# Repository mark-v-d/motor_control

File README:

Servo motor controller. Consisting of two boards, one power and one
control board. The design is made in kicad.

Working supply voltage from 50V to 650V, output current depends on used
MOSFETs but using the Rohm SCT4018 (and sufficient cooling) 20A should
not be a problem.

Currently supported encoders:

Hiperface (make sure to set the powersupply voltage to 8V instead of 12V)
Mitubishi HC-MFS and HC-PQ
CUI AMT213A-V

Additionally linear scales using incremental encoders and index pulses
can be used.

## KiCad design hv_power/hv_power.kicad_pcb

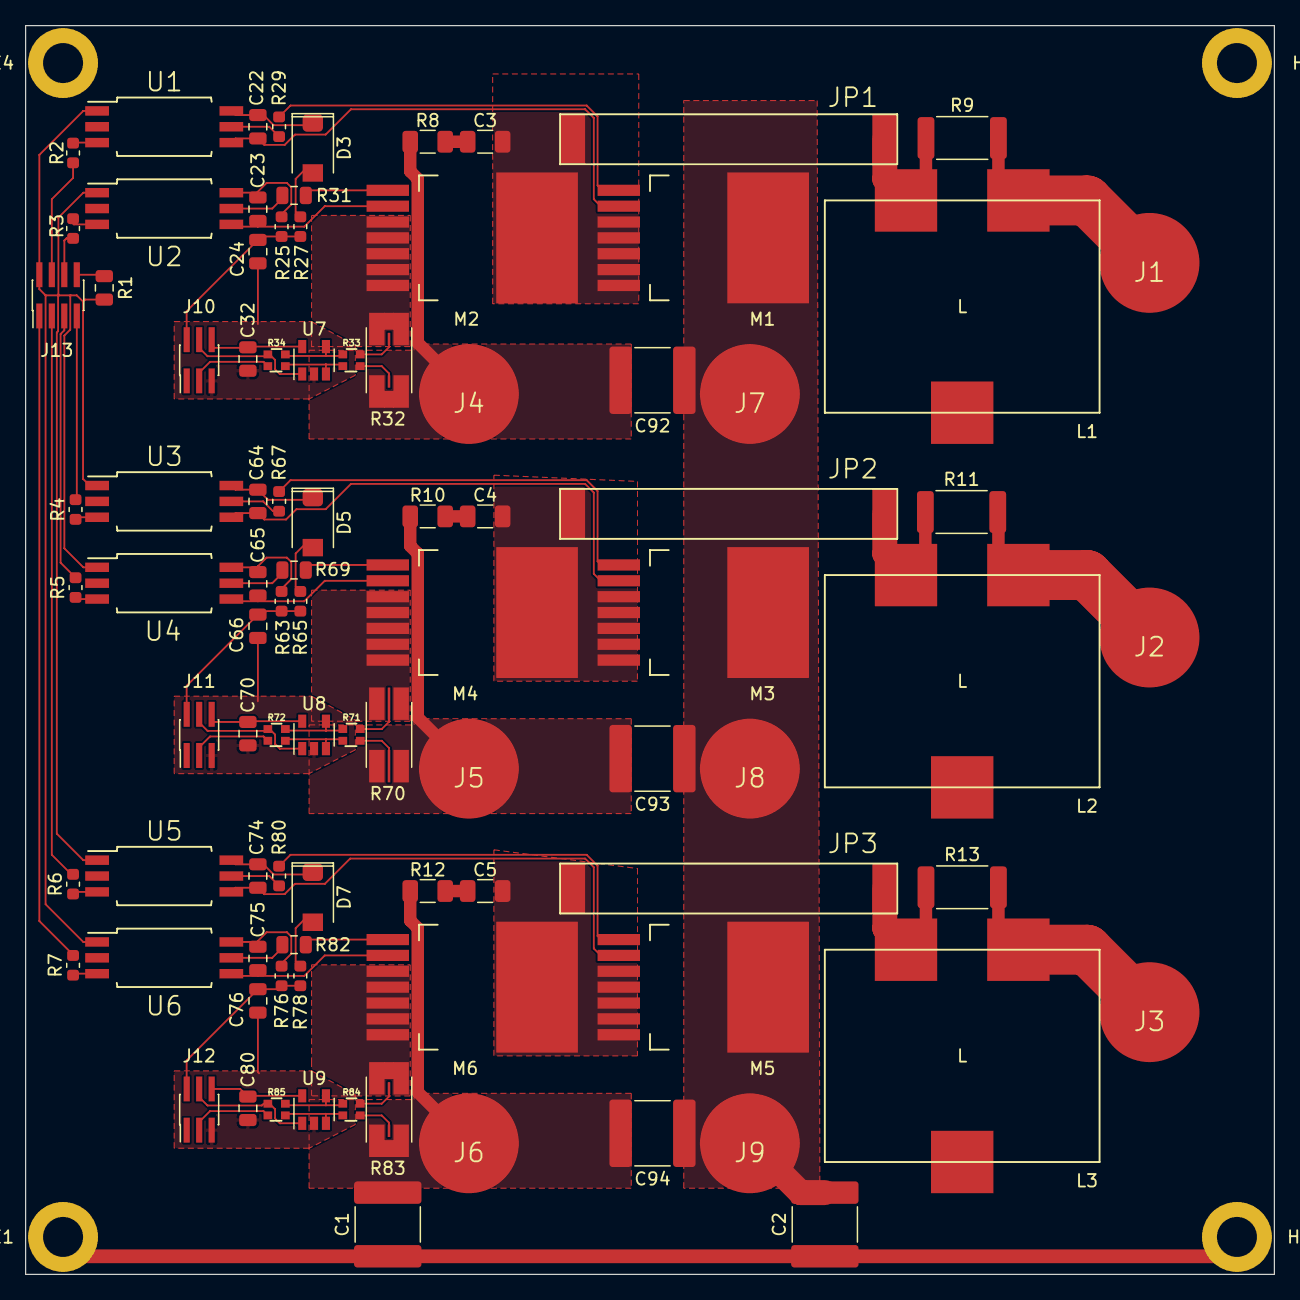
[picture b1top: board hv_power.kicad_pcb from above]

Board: 2 copper layers, 100.0 x 100.0 mm, 95 parts (0 on the bottom side), 88 nets.

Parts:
C1, C2: 3.3nF; C_2220_5650Metric
C3, C4, C5: C; C_1206_3216Metric
C22, C23, C24, C64, C65, C66, C74, C75, C76: 1uF; C_0805_2012Metric
C32, C70, C80: 100nF; C_0805_2012Metric
C92, C93, C94: 100nF; C_2220_5650Metric
D3, D5, D7: STTH112A; D_SMA
HOLE1, HOLE4: HOLE; MountingHole_3.2mm_M3_DIN965_Pad
HOLE2, HOLE3: HOLE; MountingHole_3.2mm_M3_DIN965_Pad_ScreenAlignment
J1, J2, J3: Conn_01x01_Male; Wurth_7466204
J4, J5, J6: V-; Wurth_7466204
J7, J8, J9: V+; Wurth_7466204
J10, J11, J12: Conn_02x03_Odd_Even; PinHeader_2x03_P1.00mm_Vertical_SMD
J13: Conn_02x04_Odd_Even; PinHeader_2x04_P1.00mm_Vertical_SMD
JP1, JP2, JP3: Jumper_2_Bridged; jumper_3x25mm
L1, L2, L3: L; WE-HCF2013
M1, M2, M3, M4, M5, M6: TBD; TO-263-7-GDSKS_novias
R1: NTC; R_0805_2012Metric
R2, R3, R4, R5, R6, R7: 270; R_0603_1608Metric
R8, R10, R12: R; R_1206_3216Metric
R9, R11, R13: 270; R_2512_6332Metric
R25, R27, R29, R63, R65, R67, R76, R78, R80: 4.7; R_0603_1608Metric
R31, R69, R82: 4.7; R_0805_2012Metric
R32, R70, R83: R_Shunt; R_2512_Shunt_Rohm_PMR100_3.0m
R33, R71, R84: 100; ACASN
R34, R72, R85: 2k; ACASN
U1, U2, U3, U4, U5, U6: UCC23511DWY; SOIC-6_7.5x4.68mm_P1.27mm
U7, U8, U9: TSV991ILT; SOT-23-5

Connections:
+3.3V: J13.2, R1.1, U1.1 (anode), U2.1 (anode), U3.1 (anode), U4.1 (anode), U5.1 (anode), U6.1 (anode)
+800V: C2.2, C92.1, C93.1, C94.1, J7.1, J8.1, J9.1, M1.D, M3.D, M5.D
/HBH0: J13.4, R2.2
/HBH1: J13.7, R4.2
/HBH2: J13.3, R6.2
/HBL0: J13.6, R3.2
/HBL1: J13.5, R5.2
/HBL2: J13.1, R7.2
/H_Bridge0/0: C24.1, C32.2, J10.5, U7.2 (V-)
/H_Bridge0/+3.3: C32.1, J10.6, U7.5 (V+)
/H_Bridge0/+12: C24.2, J10.2, R25.2, R27.1
/H_Bridge0/CS: M2.S, R32.1
/H_Bridge0/C_N: J10.4, R34.1, U7.1
/H_Bridge0/C_P: J10.3, R34.2
/H_Bridge0/I_N: R33.1, R34.4, U7.4 (-)
/H_Bridge0/I_P: R33.2, R34.3, U7.3 (+)
/H_Bridge0/V-: C92.2, J4.1, R8.2, R32.4
/H_Bridge0/d1: R2.1, U1.3 (cathode)
/H_Bridge0/d2: R3.1, U2.3 (cathode)
/H_Bridge0/sw: C3.1, JP1.1 (A), M1.S, M2.D
/H_Bridge0/sw_+: C22.1, D3.C, U1.6 (vcc)
/H_Bridge0/sw_g: M1.G, R29.1
/H_Bridge0/sw_m1: JP1.2 (B), L1.2, R9.1
/H_Bridge0/sw_m2: J1.1, L1.1, R9.2
/H_Bridge0/sw_o: R29.2, U1.5 (out)
/H_Bridge0/sw_s: C22.2, M1.KS (ks), U1.4 (gnd)
/H_Bridge0/x: C3.2, R8.1
/H_Bridge1/0: C66.1, C70.2, J11.5, U8.2 (V-)
/H_Bridge1/+3.3: C70.1, J11.6, U8.5 (V+)
/H_Bridge1/+12: C66.2, J11.2, R63.2, R65.1
/H_Bridge1/CS: M4.S, R70.1
/H_Bridge1/C_N: J11.4, R72.1, U8.1
/H_Bridge1/C_P: J11.3, R72.2
/H_Bridge1/I_N: R71.1, R72.4, U8.4 (-)
/H_Bridge1/I_P: R71.2, R72.3, U8.3 (+)
/H_Bridge1/V-: C93.2, J5.1, R10.2, R70.4
/H_Bridge1/d1: R4.1, U3.3 (cathode)
/H_Bridge1/d2: R5.1, U4.3 (cathode)
/H_Bridge1/sw: C4.1, JP2.1 (A), M3.S, M4.D
/H_Bridge1/sw_+: C64.1, D5.C, U3.6 (vcc)
/H_Bridge1/sw_g: M3.G, R67.1
/H_Bridge1/sw_m1: JP2.2 (B), L2.2, R11.1
/H_Bridge1/sw_m2: J2.1, L2.1, R11.2
/H_Bridge1/sw_o: R67.2, U3.5 (out)
/H_Bridge1/sw_s: C64.2, M3.KS (ks), U3.4 (gnd)
/H_Bridge1/x: C4.2, R10.1
/H_Bridge2/0: C76.1, C80.2, J12.5, U9.2 (V-)
/H_Bridge2/+3.3: C80.1, J12.6, U9.5 (V+)
/H_Bridge2/+12: C76.2, J12.2, R76.2, R78.1
/H_Bridge2/CS: M6.S, R83.1
/H_Bridge2/C_N: J12.4, R85.1, U9.1
/H_Bridge2/C_P: J12.3, R85.2
/H_Bridge2/I_N: R84.1, R85.4, U9.4 (-)
/H_Bridge2/I_P: R84.2, R85.3, U9.3 (+)
/H_Bridge2/V-: C1.2, C94.2, J6.1, R12.2, R83.4
/H_Bridge2/d1: R6.1, U5.3 (cathode)
/H_Bridge2/d2: R7.1, U6.3 (cathode)
/H_Bridge2/sw: C5.1, JP3.1 (A), M5.S, M6.D
/H_Bridge2/sw_+: C74.1, D7.C, U5.6 (vcc)
/H_Bridge2/sw_g: M5.G, R80.1
/H_Bridge2/sw_m1: JP3.2 (B), L3.2, R13.1
/H_Bridge2/sw_m2: J3.1, L3.1, R13.2
/H_Bridge2/sw_o: R80.2, U5.5 (out)
/H_Bridge2/sw_s: C74.2, M5.KS (ks), U5.4 (gnd)
/H_Bridge2/x: C5.2, R12.1
/ntc: J13.8, R1.2
/pe: C1.1, C2.1, HOLE1.1, HOLE2.1
unnamed: D3.A, R27.2
unnamed: D5.A, R65.2
unnamed: D7.A, R78.2
unnamed: M2.G, R31.1
unnamed: C23.2, M2.KS (ks), U2.4 (gnd)
unnamed: M4.G, R69.1
unnamed: C65.2, M4.KS (ks), U4.4 (gnd)
unnamed: M6.G, R82.1
unnamed: C75.2, M6.KS (ks), U6.4 (gnd)
unnamed: R32.2, R33.4
unnamed: R32.3, R33.3
unnamed: R70.2, R71.4
unnamed: R70.3, R71.3
unnamed: R83.2, R84.4
unnamed: R83.3, R84.3
unnamed: R31.2, U2.5 (out)
unnamed: C23.1, R25.1, U2.6 (vcc)
unnamed: R69.2, U4.5 (out)
unnamed: C65.1, R63.1, U4.6 (vcc)
unnamed: R82.2, U6.5 (out)
unnamed: C75.1, R76.1, U6.6 (vcc)

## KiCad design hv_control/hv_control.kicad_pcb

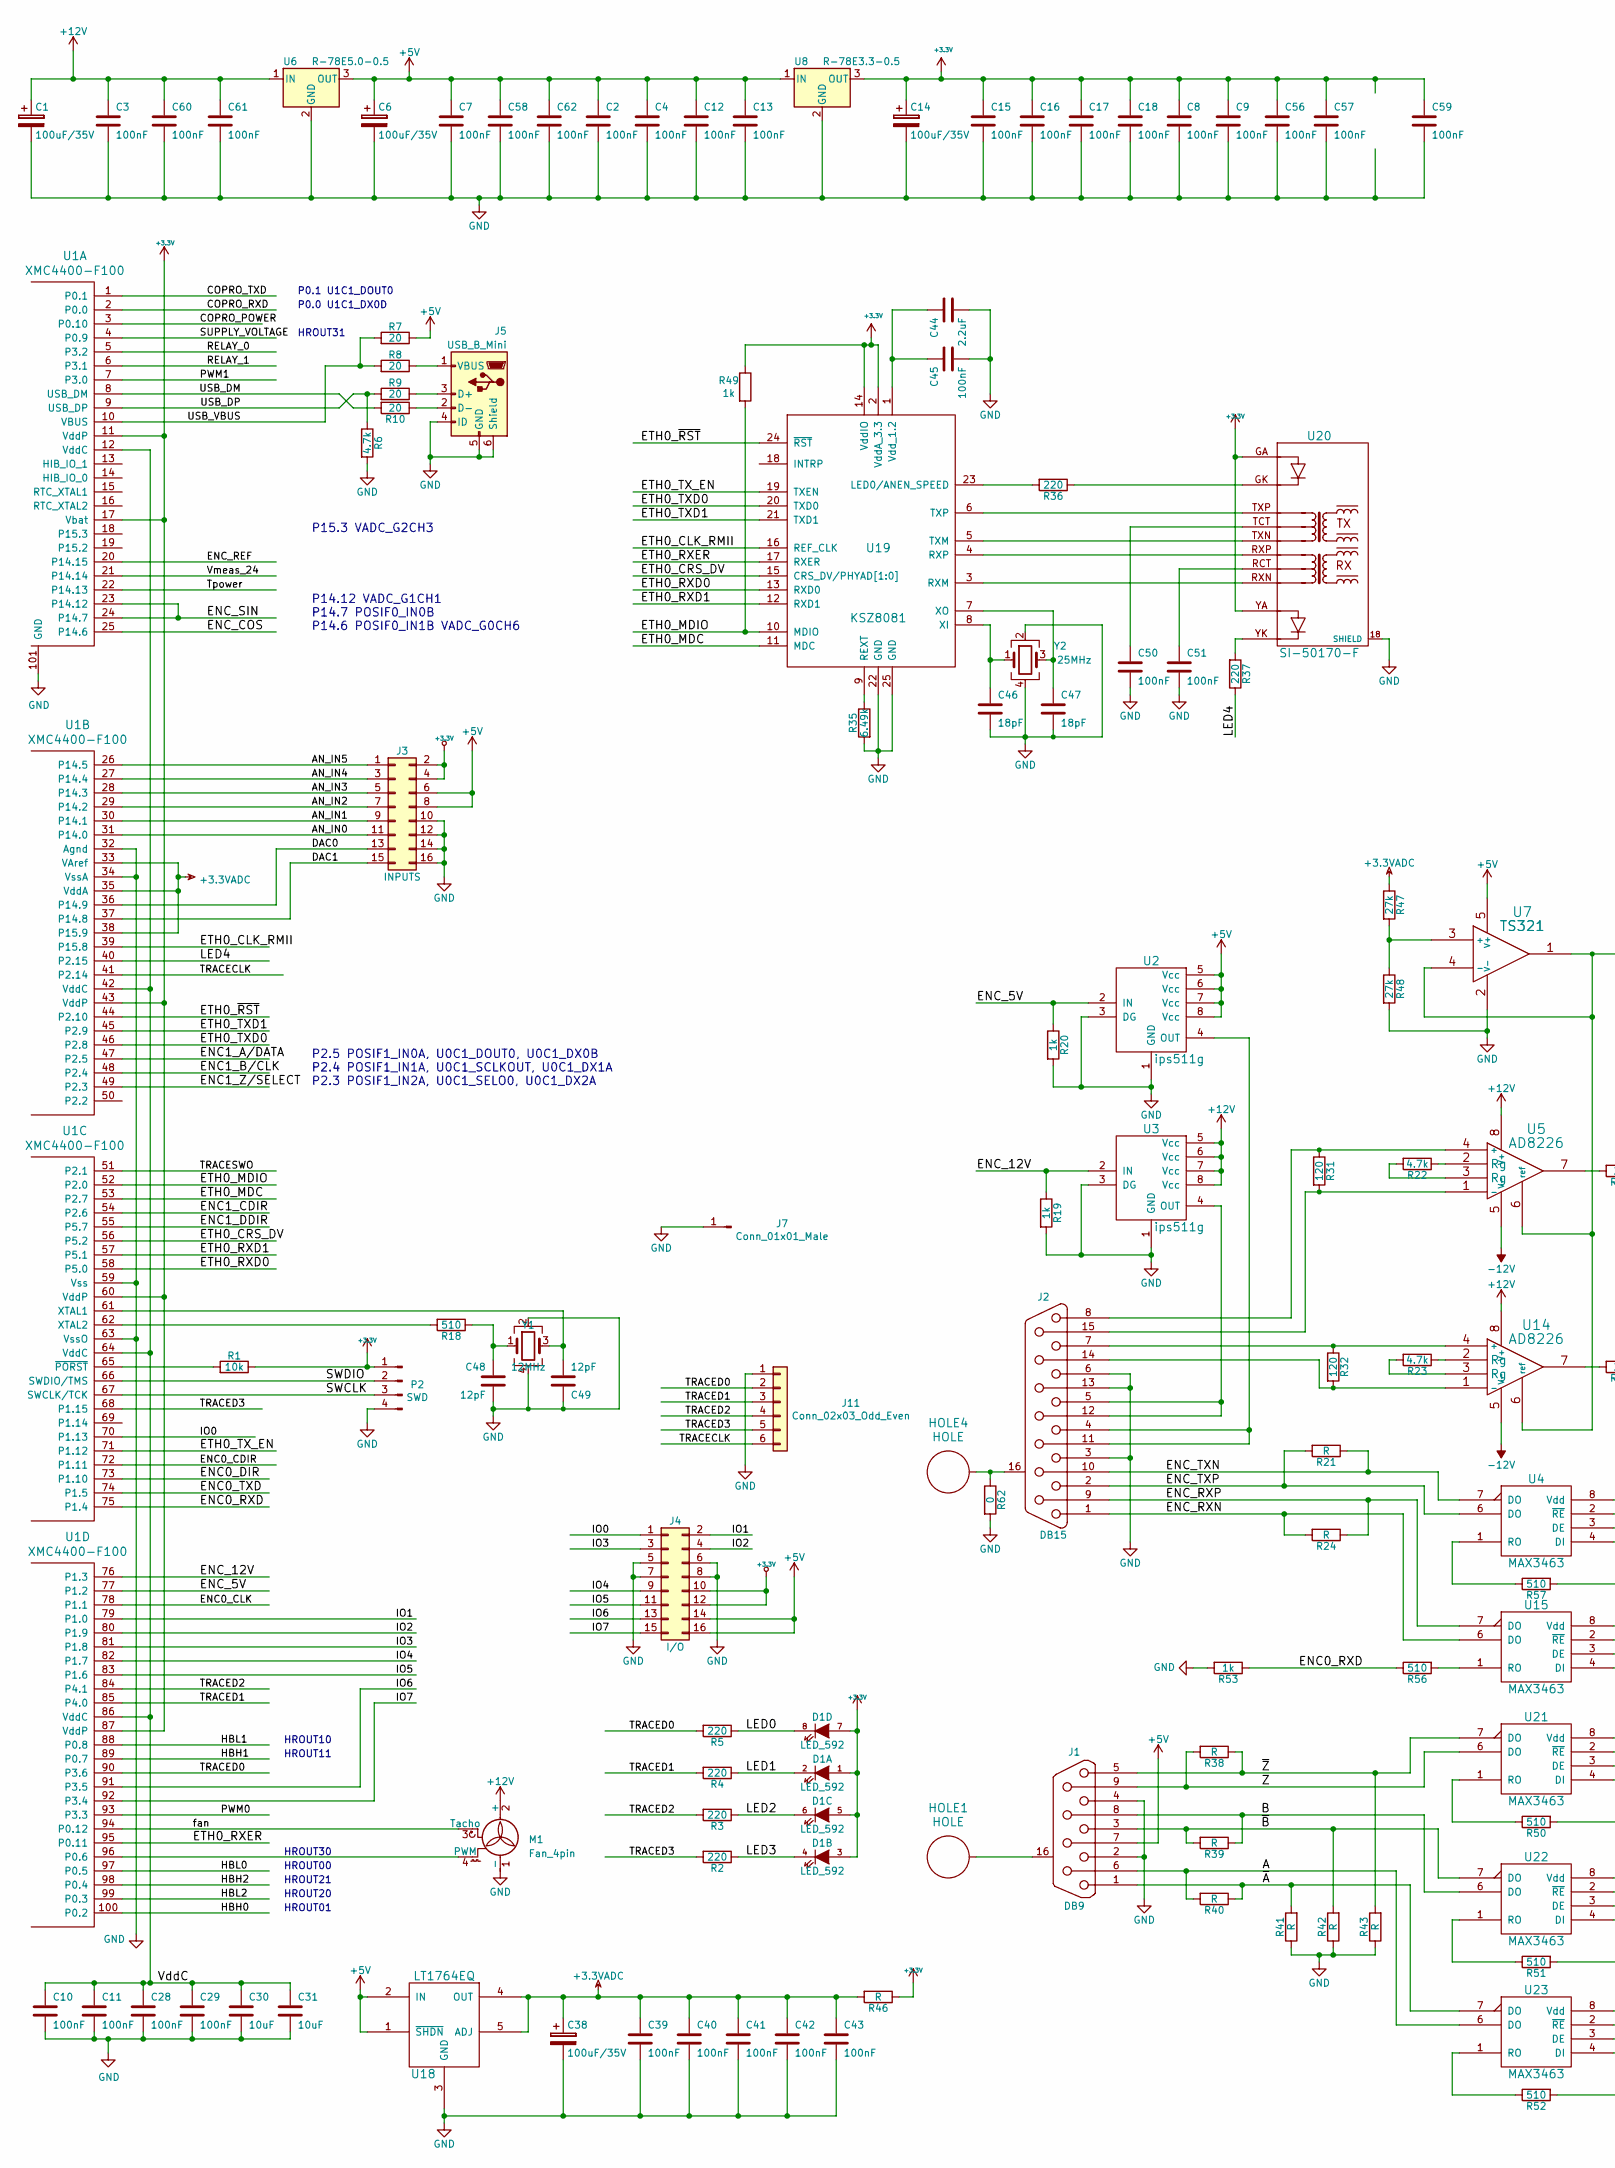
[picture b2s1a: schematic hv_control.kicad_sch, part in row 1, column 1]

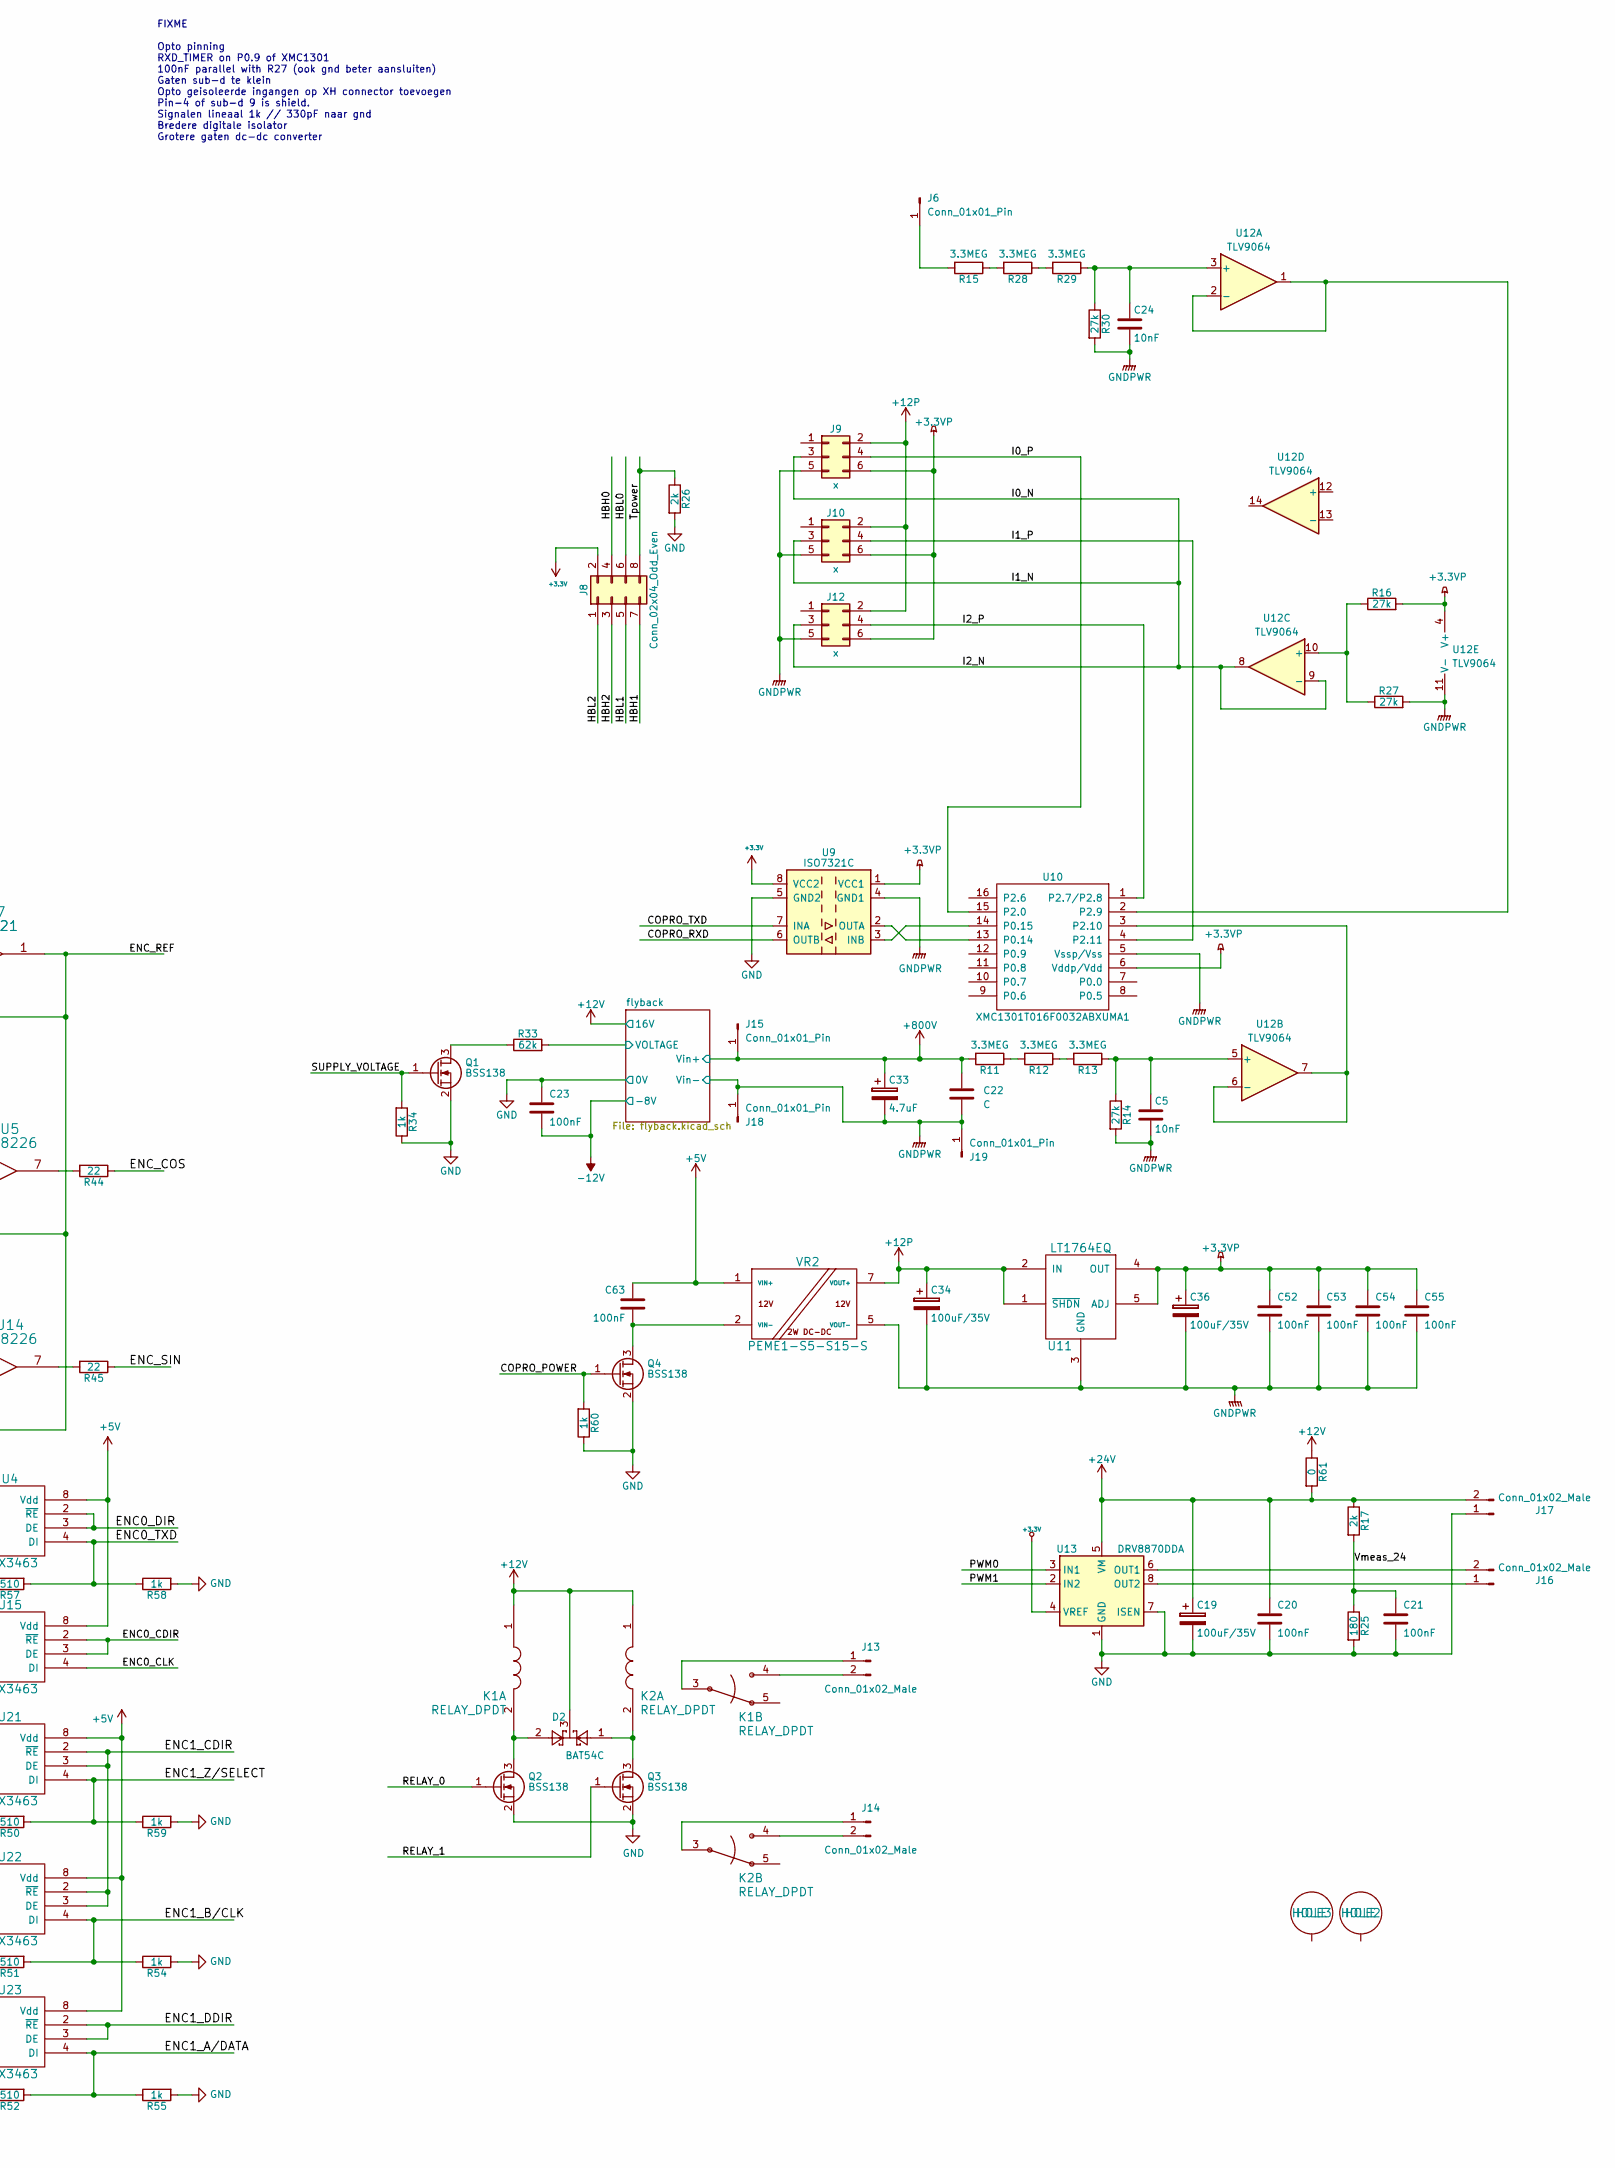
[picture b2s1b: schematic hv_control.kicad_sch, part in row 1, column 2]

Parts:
C1, C6, C14, C19, C34, C36, C38: 100uF/35V; CP_Elec_8x10.5; PartNr EEEFK1V101P
C2, C3, C4, C7, C8, C9, C10, C11, C12, C13, C15, C16, C17, C18, C20, C21, C23, C28, C29, C39, C40, C41, C42, C43, C45, C50, C51, C52, C54, C55, C56, C57, C58, C59, C60, C61, C62, C63: 100nF; C_0603_1608Metric
C5, C24: 10nF; C_0603_1608Metric
C22: C; C_Rect_L18.0mm_W6.0mm_P15.00mm_FKS3_FKP3
C30, C31: 10uF; C_1210_3225Metric
C33: 4.7uF; CP_Elec_10x14.3; PartNr EEVEB2G4R7Q
C44: 2.2uF; C_1206_3216Metric
C46, C47: 18pF; C_0603_1608Metric
C48, C49: 12pF; C_0603_1608Metric
C53: 100nF; C_0805_2012Metric
D1: LED_592; LED_592-3030-013F
D2: BAT54C; SOT-23
HOLE1, HOLE2: HOLE; MountingHole_3.2mm_M3_DIN965_Pad_ScreenAlignment
HOLE3, HOLE4: HOLE; MountingHole_3.2mm_M3_DIN965_Pad
J1: DB9; DB9F_ebay; PartNr 1734354-1; Farnell 1653978
J2: DB15; DB15F_ebay; PartNr 1-106506-2; Farnell 3417207
J3: INPUTS; PinHeader_2x08_P2.54mm_Vertical
J4: I/O; PinHeader_2x08_P2.54mm_Vertical
J5: USB_B_Mini; USB_Micro-B_Molex-105017-0001
J6, J15, J18, J19: Conn_01x01_Pin; Pin_D1.4mm_L8.5mm_W2.8mm_FlatFork
J7: Conn_01x01_Male; PinHeader_1x01_P2.54mm_Vertical
J8: Conn_02x04_Odd_Even; PinSocket_2x04_P1.00mm_Vertical_SMD; PartNr CLM-104-02-F-D; Digikey SAM15174-ND
J9, J10, J12: x; PinSocket_2x03_P1.00mm_Vertical_SMD; PartNr CLM-103-02-F-D; Digikey SAM12591-ND
J11: Conn_02x03_Odd_Even; PinHeader_1x06_P2.54mm_Vertical
J13, J14, J16, J17: Conn_01x02_Male; pin_2_5mm
K1, K2: RELAY_DPDT; T77
M1: Fan_4pin; FanPinHeader_1x04_P2.54mm_Vertical; PartNr 47053-3000; Mouser 538-47053-3000
P2: SWD; PinHeader_1x04_P2.54mm_Vertical
Q1, Q2, Q3, Q4: BSS138; SOT-23
R1: 10k; R_0603_1608Metric
R2, R3, R4, R5, R36, R37: 220; R_0603_1608Metric
R6, R22, R23: 4.7k; R_0603_1608Metric
R7: 20; R_0805_2012Metric
R8, R9, R10: 20; R_0603_1608Metric
R11, R12, R13, R15, R28, R29: 3.3MEG; R_1206_3216Metric
R14, R16, R27, R30, R47, R48: 27k; R_0603_1608Metric
R17, R26: 2k; R_0603_1608Metric
R18, R50, R51, R52, R56, R57: 510; R_0603_1608Metric
R19, R20, R34, R49, R53, R54, R55, R58, R59, R60: 1k; R_0603_1608Metric
R21, R24, R38, R39, R40, R41, R42, R43, R46: R; R_0603_1608Metric
R25: 180; R_0603_1608Metric
R31, R32: 120; R_0603_1608Metric
R33: 62k; R_0603_1608Metric
R35: 6.49k; R_0603_1608Metric
R44, R45: 22; R_0603_1608Metric
R61: 0; R_0805_2012Metric
R62: 0; R_0603_1608Metric
U1: XMC4400-F100; TQFP-100-1EP_14x14mm_P0.5mm_EP5x5mm; Farnell 2418735
U2, U3: ips511g; SOIC-8_3.9x4.9mm_P1.27mm
U4, U15, U21, U22, U23: MAX3463; SOIC-8_3.9x4.9mm_P1.27mm
U5, U14: AD8226; SOIC-8_3.9x4.9mm_P1.27mm; Farnell 1827360
U6: R-78E5.0-0.5; Converter_DCDC_RECOM_R-78E-0.5_THT
U7: TS321; SOT-23-5; PartNr TS321AILT; Farnell 1750165
U8: R-78E3.3-0.5; Converter_DCDC_RECOM_R-78E-0.5_THT
U9: ISO7321C; SOIC-8_3.9x4.9mm_P1.27mm; Digikey 296-42102-1-ND
U10: XMC1301T016F0032ABXUMA1; TSSOP-16_4.4x5mm_P0.65mm; Digikey XMC1301T016F0032ABXUMA1CT-ND
U11, U18: LT1764EQ; DD-PAK
U12: TLV9064; SOIC-14_3.9x8.7mm_P1.27mm
U13: DRV8870DDA; Texas_HTSOP-8-1EP_3.9x4.9mm_P1.27mm_EP2.95x4.9mm_Mask2.4x3.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; Digikey 296-42660-1-ND
U19: KSZ8081; QFN-24-1EP_4x4mm_P0.5mm_EP2.6x2.6mm; PartNr KSZ8081RNACA-TR; Farnell 2509802
U20: SI-50170-F; ETH100_MAG; PartNr SI-50170-F; Farnell 2676003
VR2: PEME1-S5-S15-S; RKZXXXXS; Digikey 102-6340-ND
Y1: 12MHz; Crystal_SMD_SeikoEpson_FA238-4Pin_3.2x2.5mm; PartNr QC3CA12.0000F12B23M; Farnell 2508630
Y2: 25MHz; Crystal_SMD_SeikoEpson_FA238-4Pin_3.2x2.5mm; PartNr QC3CA25.0000F18B23M; Farnell 2508942

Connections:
+3.3V: C8.1, C9.1, C14.1, C15.1, C16.1, C17.1, C18.1, C56.1, C57.1, C59.1, D1.1 (A), D1.3 (A), D1.5 (A), D1.7 (A), J3.2, J3.4, J4.10, J4.12, J8.2, P2.1, R1.1, R46.1, R49.1, U1.11 (VddP), U1.17 (Vbat), U1.43 (VddP), U1.60 (VddP), U1.87 (VddP), U8.3 (OUT), U9.8 (VCC2), U13.4 (VREF), U19.2 (VddA_3.3), U19.14 (VddIO), U20.GA, U20.YA
+3.3VADC: C38.1, C39.1, C40.1, C41.1, C42.1, C43.1, R46.2, R47.1, U1.33 (VAref), U1.35 (VddA), U1.38 (P15.9), U18.4 (OUT), U18.5 (ADJ)
+3.3VP: C36.1, C52.1, C53.1, C54.1, C55.1, J9.6, J10.6, J12.6, R16.2, U9.1 (VCC1), U10.6 (Vddp/Vdd), U11.4 (OUT), U11.5 (ADJ), U12.4 (V+)
+5V: C2.1, C4.1, C6.1, C7.1, C12.1, C13.1, C58.1, C62.1, C63.1, J1.7, J3.6, J3.8, J4.14, J4.16, R7.1, U2.5 (Vcc), U2.6 (Vcc), U2.7 (Vcc), U2.8 (Vcc), U4.8 (Vdd), U6.3 (OUT), U7.5 (V+), U8.1 (IN), U15.8 (Vdd), U18.1 (~SHDN), U18.2 (IN), U21.8 (Vdd), U22.8 (Vdd), U23.8 (Vdd), VR2.1 (VIN+)
+12P: C34.1, J9.2, J10.2, J12.2, U11.1 (~SHDN), U11.2 (IN), VR2.7 (VOUT+)
+24V: C19.1, C20.1, J17.2, R17.1, R61.2, U13.5 (VM)
+800V: C22.1, J15.1, R11.2; also elsewhere on the board
-12V: C23.2, U5.5 (V-), U14.5 (V-); also elsewhere on the board
/A: J1.6, R40.2, U23.6 (DO)
/AN_IN0: J3.11, U1.31 (P14.0)
/AN_IN1: J3.9, U1.30 (P14.1)
/AN_IN2: J3.7, U1.29 (P14.2)
/AN_IN3: J3.5, U1.28 (P14.3)
/AN_IN4: J3.3, U1.27 (P14.4)
/AN_IN5: J3.1, U1.26 (P14.5)
/B: J1.8, R39.1, U22.6 (DO)
/COPRO_POWER: Q4.1 (G), R60.2, U1.3 (P0.10)
/COPRO_RXD: U1.2 (P0.0), U9.6 (OUTB)
/COPRO_TXD: U1.1 (P0.1), U9.7 (INA)
/DAC0: J3.13, U1.36 (P14.9)
/DAC1: J3.15, U1.37 (P14.8)
/ENC0_CDIR: U1.72 (P1.11), U15.2 (~RE), U15.3 (DE)
/ENC0_CLK: U1.78 (P1.1), U15.4 (DI)
/ENC0_DIR: U1.73 (P1.10), U4.2 (~RE), U4.3 (DE)
/ENC0_RXD: R53.1, R56.1, U1.75 (P1.4)
/ENC0_TXD: R57.2, R58.1, U1.74 (P1.5), U4.4 (DI)
/ENC1_A/DATA: R52.2, R55.1, U1.47 (P2.5), U23.4 (DI)
/ENC1_B/CLK: R51.2, R54.1, U1.48 (P2.4), U22.4 (DI)
/ENC1_CDIR: U1.54 (P2.6), U21.2 (~RE), U21.3 (DE), U22.2 (~RE), U22.3 (DE)
/ENC1_DDIR: U1.55 (P5.7), U23.2 (~RE), U23.3 (DE)
/ENC1_Z/SELECT: R50.2, R59.1, U1.49 (P2.3), U21.4 (DI)
/ENC_5V: R20.1, U1.77 (P1.2), U2.2 (IN)
/ENC_12V: R19.1, U1.76 (P1.3), U3.2 (IN)
/ENC_COS: R44.1, U1.25 (P14.6)
/ENC_REF: U1.20 (P14.15), U5.6 (ref), U7.1, U7.4 (-), U14.6 (ref)
/ENC_RXN: J2.1, R24.2, U15.6 (DO)
/ENC_RXP: J2.9, R24.1, U15.7 (DO)
/ENC_SIN: R45.1, U1.23 (P14.12), U1.24 (P14.7)
/ENC_TXN: J2.10, R21.1, U4.7 (DO)
/ENC_TXP: J2.2, R21.2, U4.6 (DO)
/ETH0_CLK_RMII: U1.39 (P15.8), U19.16 (REF_CLK)
/ETH0_CRS_DV: U1.56 (P5.2), U19.15 (CRS_DV/PHYAD[1:0])
/ETH0_MDC: U1.53 (P2.7), U19.11 (MDC)
/ETH0_MDIO: R49.2, U1.52 (P2.0), U19.10 (MDIO)
/ETH0_RXD0: U1.58 (P5.0), U19.13 (RXD0)
/ETH0_RXD1: U1.57 (P5.1), U19.12 (RXD1)
/ETH0_RXER: U1.95 (P0.11), U19.17 (RXER)
/ETH0_TXD0: U1.46 (P2.8), U19.20 (TXD0)
/ETH0_TXD1: U1.45 (P2.9), U19.21 (TXD1)
/ETH0_TX_EN: U1.71 (P1.12), U19.19 (TXEN)
/ETH0_~RST: U1.44 (P2.10), U19.24 (~RST)
/HBH0: J8.4, U1.100 (P0.2)
/HBH1: J8.7, U1.89 (P0.7)
/HBH2: J8.3, U1.98 (P0.4)
/HBL0: J8.6, U1.97 (P0.5)
/HBL1: J8.5, U1.88 (P0.8)
/HBL2: J8.1, U1.99 (P0.3)
/I0_N: J9.3, J10.3, J12.3, U12.8, U12.9 (-)
/I0_P: J9.4, U10.15 (P2.0)
/I1_P: J10.4, U10.4 (P2.11)
/I2_P: J12.4, U10.1 (P2.7/P2.8)
/IO0: J4.1, U1.70 (P1.13)
/IO1: J4.2, U1.79 (P1.0)
/IO2: J4.4, U1.80 (P1.9)
/IO3: J4.3, U1.81 (P1.8)
/IO4: J4.9, U1.82 (P1.7)
/IO5: J4.11, U1.83 (P1.6)
/IO6: J4.13, U1.91 (P3.5)
/IO7: J4.15, U1.92 (P3.4)
/LED0: D1.8 (K), R5.1
/LED1: D1.2 (K), R4.1
/LED2: D1.6 (K), R3.1
/LED3: D1.4 (K), R2.1
/LED4: R37.1, U1.40 (P2.15)
/PWM0: U1.93 (P3.3), U13.3 (IN1)
/PWM1: U1.7 (P3.0), U13.2 (IN2)
/RELAY_0: Q2.1 (G), U1.5 (P3.2)
/RELAY_1: Q3.1 (G), U1.6 (P3.1)
/SWCLK: P2.3, U1.67 (SWCLK/TCK)
/SWDIO: P2.2, U1.66 (SWDIO/TMS)
/TRACECLK: J11.6, U1.41 (P2.14)
/TRACED0: J11.2, R5.2, U1.90 (P3.6)
/TRACED1: J11.3, R4.2, U1.85 (P4.0)
/TRACED2: J11.4, R3.2, U1.84 (P4.1)
/TRACED3: J11.5, R2.2, U1.68 (P1.15)
/TRACESWO: U1.51 (P2.1)
/Tpower: J8.8, R26.1, U1.22 (P14.13)
/USB_DM: R10.2, U1.8 (USB_DM)
/USB_DP: R6.1, R9.2, U1.9 (USB_DP)
/USB_VBUS: R7.2, R8.2, U1.10 (VBUS)
/VddC: C10.1, C11.1, C28.1, C29.1, C30.1, C31.1, U1.12 (VddC), U1.42 (VddC), U1.64 (VddC), U1.86 (VddC)
/Vmeas_24: C21.1, R17.2, R25.1, U1.21 (P14.14)
/Z: J1.9, R38.2, U21.6 (DO)
/fan: M1.3 (Tacho), U1.94 (P0.12)
/flyback/VOLTAGE: R33.2; also elsewhere on the board
/~A: J1.1, R40.1, R41.2, U23.7 (DO)
/~B: J1.3, R39.2, R42.2, U22.7 (DO)
/~Z: J1.5, R38.1, R43.2, U21.7 (DO)
GNDPWR: C5.2, C22.2, C24.2, C34.2, C36.2, C52.2, C53.2, C54.2, C55.2, J9.5, J10.5, J12.5, J18.1, J19.1, R14.2, R27.2, R30.2, U9.4 (GND1), U10.5 (Vssp/Vss), U11.3 (GND), U12.11 (V-), VR2.5 (VOUT-); also elsewhere on the board
unnamed: C48.1, R18.1, Y1.1
unnamed: C50.1, U20.TCT
unnamed: C51.1, U20.RCT
unnamed: HOLE1.1, J1.16
unnamed: HOLE4.1, J2.16, R62.1
unnamed: J2.5, J2.12, U3.4 (OUT)
unnamed: J2.14, R32.2, U14.1 (-)
unnamed: J2.15, R31.2, U5.1 (-)
unnamed: J2.4, J2.11 (P111), U2.4 (OUT)
unnamed: J5.3 (D+), R9.1
unnamed: J5.2 (D-), R10.1
unnamed: J5.1 (VBUS), R8.1
unnamed: J6.1, R15.2
unnamed: J13.1, K1.3 (common)
unnamed: J13.2, K1.4 (break)
unnamed: J14.1, K2.3 (common)
unnamed: J14.2, K2.4 (break)
unnamed: J16.1, U13.8 (OUT2)
unnamed: J16.2, U13.6 (OUT1)
unnamed: D2.2, K1.2 (a2), Q2.3 (D)
unnamed: D2.1, K2.2 (a2), Q3.3 (D)
unnamed: M1.4 (PWM), U1.96 (P0.6)
unnamed: C63.2, Q4.3 (D), VR2.2 (VIN-)
unnamed: R11.1, R12.2
unnamed: R12.1, R13.2
unnamed: R15.1, R28.2
unnamed: R22.1, U5.2 (Rg)
unnamed: R22.2, U5.3 (Rg)
unnamed: R23.1, U14.2 (Rg)
unnamed: R23.2, U14.3 (Rg)
unnamed: R28.1, R29.2
unnamed: R36.1, U20.GK
unnamed: R37.2, U20.YK
unnamed: R44.2, U5.7
unnamed: R45.2, U14.7
unnamed: C49.2, U1.61 (XTAL1), Y1.3
unnamed: R18.2, U1.62 (XTAL2)
unnamed: R1.2, U1.65 (~PORST)
unnamed: R57.1, U4.1 (RO)
unnamed: J2.8, R31.1, U5.4 (+)
unnamed: R47.2, R48.1, U7.3 (+)
unnamed: U9.2 (OUTA), U10.13 (P0.14)
unnamed: U9.3 (INB), U10.14 (P0.15)
unnamed: U10.2 (P2.9), U12.1, U12.2 (-)
unnamed: U10.3 (P2.10), U12.6 (-), U12.7
unnamed: C24.1, R29.1, R30.1, U12.3 (+)
unnamed: C5.1, R13.1, R14.1, U12.5 (+)
unnamed: R16.1, R27.1, U12.10 (+)
unnamed: J2.7, R32.1, U14.4 (+)
unnamed: R56.2, U15.1 (RO)
unnamed: R36.2, U19.23 (LED0/ANEN_SPEED)
unnamed: R35.1, U19.9 (REXT)
unnamed: U19.3 (RXM), U20.RXN
unnamed: U19.4 (RXP), U20.RXP
unnamed: U19.5 (TXM), U20.TXN
unnamed: U19.6 (TXP), U20.TXP
unnamed: C44.1, C45.1, U19.1 (Vdd_1.2)
unnamed: C46.1, U19.8 (XI), Y2.1
unnamed: C47.1, U19.7 (XO), Y2.3
unnamed: R50.1, U21.1 (RO)
unnamed: R51.1, U22.1 (RO)
unnamed: R52.1, U23.1 (RO)

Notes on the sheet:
HROUT00
HROUT30
HROUT31
FIXME Opto pinning RXD_TIMER on P0.9 of XMC1301 100nF parallel with R27 (ook gnd beter aansluiten) Gaten sub-d te klein Opto geisoleerde ingangen op XH connector toevoegen Pin-4 of sub-d 9 is shield. Signalen lineaal 1k // 330pF naar gnd Bredere digitale isolator Grotere gaten dc-dc converter
HROUT10
HROUT01
P14.12 VADC_G1CH1 P14.7 POSIF0_IN0B P14.6 POSIF0_IN1B VADC_G0CH6
HROUT20
HROUT21
P15.3 VADC_G2CH3
HROUT11
P0.1 U1C1_DOUT0
P0.0 U1C1_DX0D
P2.5 POSIF1_IN0A, U0C1_DOUT0, U0C1_DX0B P2.4 POSIF1_IN1A, U0C1_SCLKOUT, U0C1_DX1A P2.3 POSIF1_IN2A, U0C1_SELO0, U0C1_DX2A

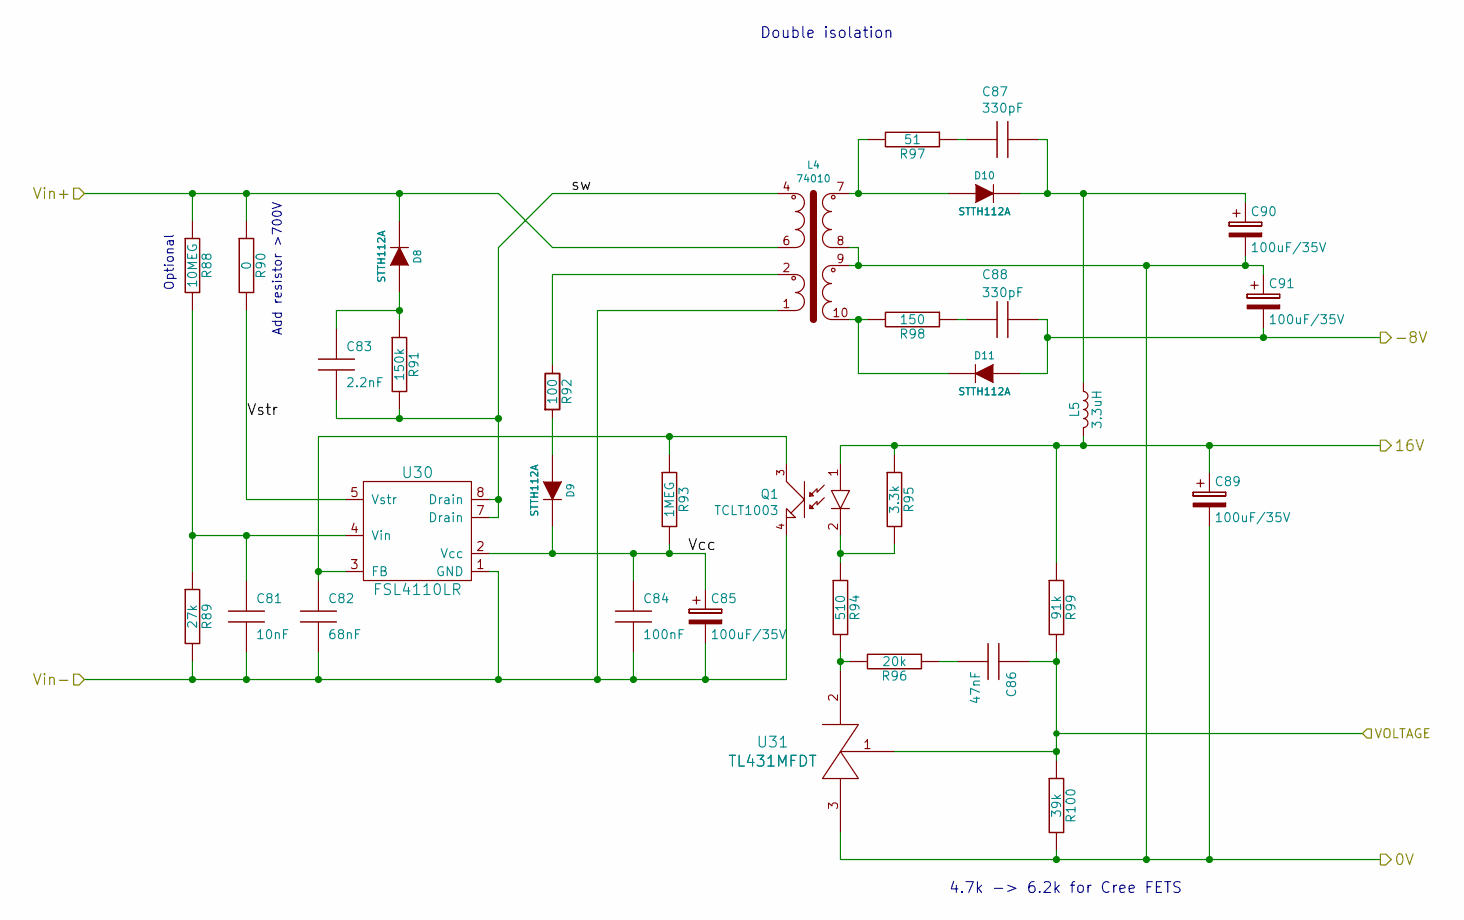
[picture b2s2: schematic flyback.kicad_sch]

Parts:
C81: 10nF; C_0603_1608Metric; Mouser 80-C0603C103K5REAUTO
C82: 68nF; C_0603_1608Metric
C83: 2.2nF; C_1206_3216Metric; PartNr 1206J1K00222KJT; Digikey 311-1511-1-ND
C84: 100nF; C_0603_1608Metric
C85, C89, C90, C91: 100uF/35V; CP_Elec_8x10.5; PartNr EEEFK1V101P
C86: 47nF; C_0603_1608Metric
C87, C88: 330pF; C_0603_1608Metric
D8: STTH112A; D_SMA; PartNr STTH112A; Farnell 2341589
D9, D10, D11: STTH112A; D_SMA; PartNr STTH112A; Digikey 497-8048-1-ND
L4: 74010; Myrra_EE16; PartNr 74010; Farnell 1214645
L5: 3.3uH; L_Coilcraft_ME3220; PartNr ME3220-332MLB; Mouser 994-ME3220-332MLB
Q1: TCLT1003; SOP-4_3.8x7.5mm_P2.54mm; PartNr TCLT1003; Mouser 782-TCLT1003
R88: 10MEG; R_1206_3216Metric; Farnell 2470930
R89: 27k; R_0603_1608Metric
R90: 0; R_1206_3216Metric; PartNr CHV1206-FX-1003ELF; Farnell 2470926
R91: 150k; R_2010_5025Metric; PartNr 3520150KJT; Digikey A102501CT-ND
R92: 100; R_0603_1608Metric
R93: 1MEG; R_0603_1608Metric
R94: 510; R_0603_1608Metric
R95: 3.3k; R_0603_1608Metric
R96: 20k; R_0603_1608Metric
R97: 51; R_0603_1608Metric
R98: 150; R_0603_1608Metric
R99: 91k; R_0603_1608Metric
R100: 39k; R_0603_1608Metric
U30: FSL4110LR; DIP-8-N6_W7.62mm; PartNr FSL4110LRN; Digikey FSL4110LRN-ND
U31: TL431MFDT; SOT-23; Farnell 2575136

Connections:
+800V: D8.C, L4.6, R88.1, R90.1; also elsewhere on the board
-12V: C88.1, C91.2, D11.A; also elsewhere on the board
/flyback/VOLTAGE: C86.1, R99.2, R100.1, U31.1 (ref); also elsewhere on the board
/flyback/Vcc: C84.1, C85.1, D9.C, R93.2, U30.2 (Vcc)
/flyback/Vstr: R90.2, U30.5 (Vstr)
/flyback/sw: C83.2, L4.4, R91.2, U30.7 (Drain), U30.8 (Drain)
GNDPWR: C81.2, C82.2, C84.2, C85.2, L4.1, Q1.4 (E), R89.2, U30.1 (GND); also elsewhere on the board
unnamed: C83.1, D8.A, R91.1
unnamed: C86.2, R96.1
unnamed: C87.1, C90.1, D10.C, L5.1
unnamed: C87.2, R97.1
unnamed: C88.2, R98.1
unnamed: D9.A, R92.2
unnamed: D10.A, L4.7, R97.2
unnamed: D11.C, L4.10, R98.2
unnamed: L4.2, R92.1
unnamed: C81.1, R88.2, R89.1, U30.4 (Vin)
unnamed: R94.2, R96.2, U31.2 (C)

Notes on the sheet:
Double isolation
Add resistor >700V
4.7k -> 6.2k for Cree FETS
Optional

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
